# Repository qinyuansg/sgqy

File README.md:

# 🏠 HomeHero — Daily Tasks for House Helpers

> **Also in this repo:** [`fastpass/`](fastpass/) — the AGIL® Secure FastPass product site (kerb-to-gate journey explorer, traveller app demo, command console). See [`fastpass/README.md`](fastpass/README.md).

A simple, warm, mobile-first web app that helps a house helper know **what to do today**, tick tasks as done, and explain (in one tap) when something cannot be done — while giving the household full transparency on progress.

**Zero install, zero backend, zero cost.** Open `index.html` in any phone browser (or host it on GitHub Pages) and it just works. All data is saved on the device.

---

## Product vision (CPO perspective)

### The problem
Households coordinate daily chores with helpers through memory, paper lists, or long chat messages. Helpers — often with limited literacy and low tech confidence — struggle with text-heavy apps, and employers lack visibility into what got done and *why* something didn't.

### The users
| Persona | Need |
|---|---|
| **The Helper** (primary) | "Show me clearly what to do *now*, let me finish tasks with one tap, and make it feel good." |
| **The Employer** (secondary) | "Set up the routine once, then see progress and reasons transparently — without nagging." |

### Design principles
1. **Zero reading required to succeed.** Every task has a big emoji; every action is one large tap; reasons for "cannot do" are picture buttons, and typing is always optional.
2. **Time is the navigation.** The day flows visually Morning → Noon → Afternoon → Night with a colored timeline, a pulsing **NOW** badge, and auto-scroll to the current period. The helper never asks "what's next?"
3. **Every action gets a reward.** Apple-style spring animations, a drawn checkmark, a flying ⭐ +1, confetti bursts, haptic vibration, and a full celebration when the day is complete. Positive loops, never guilt.
4. **Honesty is a feature, not a failure.** "Cannot 😕" is a first-class button. Reporting a blocker (no supplies, machine broken…) earns a friendly "thank you for telling" — because a true status is more valuable than a fake tick.
5. **Transparency without surveillance.** The 7-day history shows completion bars and remarks for both parties. No GPS, no photos, no timers — trust-building, not policing.

---

## MVP features

- **⏰ Time-flow timeline** — tasks grouped Morning 🌅 / Noon ☀️ / Afternoon 🌤️ / Night 🌙 with a gradient timeline, current-period highlight, and auto-scroll.
- **✓ One-tap completion** — giant 58px tick button, springy checkmark draw, confetti, star reward, done timestamp. Tap again to undo mistakes.
- **😕 "Cannot do" flow** — bottom sheet with four picture reasons (🧴 no supplies, ⏰ no time, 🤒 not well, 🔧 broken) + optional free-text remark.
- **🎮 Gamification** — daily progress ring (Apple-Fitness style), ⭐ stars per task, 🔥 day streak for days where every task is actioned (done *or* honestly reported), escalating encouragement messages, full-screen celebration with confetti rain.
- **🔔 Reminders** — one tap on the bell enables browser notifications at the start of each period listing what's pending (fires while the app is open; see roadmap for push).
- **📅 Transparency** — 7-day history with completion bars, trophies for perfect days, and every "cannot do" reason surfaced with its remark.
- **⚙️ Employer setup** — manage the task list in-app: emoji picker, task name, time period. Changes apply instantly, persisted on-device.
- **📱 Installable** — web-app manifest lets it live on the home screen like a native app.

## Deliberate MVP cuts (roadmap)

| Next | Why later |
|---|---|
| Multi-language (Bahasa, Tagalog, Burmese, Sinhala…) | Highest-impact v1.1; the emoji-first UI keeps v1 usable meanwhile |
| Cloud sync + employer's own phone view | Needs accounts/backend; MVP proves the loop on one shared device |
| True push reminders (service worker / server push) | Browser limitations; in-app notifications validate the habit first |
| Photo proof (optional per task) | Useful but risks a surveillance feel — needs careful design |
| Weekly/rotating schedules (e.g. "change bedsheets — Mondays") | Data model supports it; UI simplicity first |
| Rewards marketplace (stars → real treats agreed with employer) | Requires employer buy-in mechanics |

## Success metrics
- **Activation:** helper completes ≥1 task on day one.
- **Habit:** ≥5 of 7 days with ≥80% tasks actioned (done *or* honestly skipped).
- **Trust:** share of skipped tasks carrying a reason (target: 100% — it's mandatory by design).
- **Delight proxy:** streak length distribution.

---

## Run & share it

**Easiest — share one file (works 100% offline):**
Send **`HomeHero.html`** to anyone over WhatsApp, email, or USB. They open it in any browser — no internet, no install, no other files needed. Progress saves on their own device. Rebuild it after changing the app:

```bash
python3 tools/build_single_file.py
```

**Hosted — GitHub Pages (offline after first visit):**
Enable Pages on this repo (Settings → Pages → deploy from branch), open the URL on the helper's phone, and "Add to Home Screen". A service worker (`sw.js`) caches the app, so it launches and works fully offline from then on.

**Local dev:**
```bash
python3 -m http.server 8000   # then visit http://localhost:8000
```

> Note: each device keeps its own data (tasks, progress, remarks) in `localStorage` — sharing the file shares the app, not the data. Cross-device sync is on the roadmap.

## Tech notes

- Vanilla HTML/CSS/JS — no build step, no dependencies, works offline after first load.
- Apple-inspired design system: iOS system palette, SF font stack, frosted-glass top bar, spring easing (`cubic-bezier(0.34, 1.56, 0.64, 1)`), 44pt+ touch targets, `prefers-reduced-motion` respected.
- State in `localStorage`: task list, per-day completion log (status/reason/remark/time), streak, reminder preference.

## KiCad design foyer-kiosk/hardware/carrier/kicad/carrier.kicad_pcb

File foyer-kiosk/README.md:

# Foyer VK-1 — visitor enrolment kiosk

A compact, premium self-service check-in kiosk for corporate office lobbies.
A visitor scans their invitation QR code (or registers as a walk-up), scans a
passport or ID card (OCR + NFC chip), has a face photo taken with liveness
detection, accepts the site rules, and gets a printed badge or mobile pass
while their host is notified through the visitor management system (VMS).

| | |
|---|---|
| Core unit | 250 W × 640 H × 200 D mm, ≈ 11 kg, anodised aluminium + 4 mm edge-to-edge glass |
| Compute | Raspberry Pi Compute Module 5 (4 GB / 32 GB eMMC, Wi-Fi 5 + BT 5.0), supply until ≥ Jan 2036 |
| Display | 13.3" 1920 × 1080 PCAP, portrait (Elo 1302L) |
| Identity | Full-page passport / ID reader, OCR + ePassport RFID (DESKO PENTA 4X Cube) |
| Face | RGB + NoIR 12 MP cameras with 850 nm IR flood for liveness |
| Invitation | Zebra DS55 2D scanner (reads QR from phone screens) |
| Badges | 80 mm thermal kiosk printer with cutter on a slide-out drawer |
| Audio | I2S class-D amplifier + speaker, 2 × I2S MEMS microphones (call reception) |
| Approach / status | ToF presence sensor, 24-LED status light bar |
| Connectivity | Gigabit Ethernet, Wi-Fi 2.4/5 GHz, Bluetooth; options: LTE fallback, HID NFC encoder |
| Power | Single PoE++ cable (802.3bt Type 4) or USB-C PD ≥ 65 W |
| Mounting | One core unit on desk, wall or floor kit (shared hang-on mount plate) |
| Security / privacy | Secure boot + full-disk encryption (CM5 OTP key), ATECC608B device identity, no PII at rest after sync |

## Repository map

```
foyer-kiosk/
├── hardware/
│   ├── interface-contract.md     HW⇄SW contract: buses, GPIOs, power policy (rev B)
│   ├── eda/                      circuit-as-code toolkit (ERC, schematic gen, PCB build, routing, DRC, fab)
│   ├── power/design_calcs.py     power-stage calculations (→ docs/power-design.md)
│   ├── carrier/                  FYR-CB-01 carrier board: carrier.py (circuit), build.py (layout+fab),
│   │                             kicad/ (KiCad 7 project), fab/ (gerbers, drill, BOM, CPL, STEP, PDFs)
│   ├── sensorbar/                FYR-SB-01 sensor bar: same structure
│   └── lib/                      vendored symbols + Foyer footprints (incl. CM5 socket)
├── mechanical/
│   ├── enclosure.py              parametric CadQuery model (enclosure + kits)
│   ├── build.py                  exports below
│   └── out/  step/ print/ dxf/ drawings/ renders/
├── software/                     enrolment app, device agent, OS image build (see software/README.md)
└── docs/                         spec, BOM, installation guide, maintenance manual, manufacturing,
                                  verification register, power design
```

## Requirement trace

| Requirement | How it is met | Where |
|---|---|---|
| Compact, modern, premium | 250 mm wide, edge-to-edge glass, anodised aluminium, no visible fasteners (lock hidden under the door lip, security screw under the mount) | `mechanical/`, renders |
| Locked-down kiosk OS, boots into the app | Raspberry Pi OS (arm64) image with cage + Chromium kiosk, hardened services | `software/os-image/` |
| QR or walk-up → ID + face → VMS → host notified → badge / mobile pass | Enrolment app + device agent with VMS adapter | `software/app`, `software/agent` |
| Publicly available, long-term compute | Raspberry Pi CM5, production to ≥ 2036 | `docs/bom-system.csv` |
| 10–13" portrait touch | 13.3" PCAP portrait | Elo 1302L |
| Camera with liveness | RGB + NoIR IMX708 pair + 850 nm IR flood on the sensor bar | `hardware/sensorbar` |
| QR reader, ID/passport reader (OCR + NFC), badge printer | DS55, DESKO PENTA 4X, Custom VKP80III; carrier USB 2 ×6 + USB 3 ×1 internal ports | carrier `J9–J12` |
| Speaker + mic | MAX98357A I2S amp + speaker header; 2 × ICS-43434 | carrier `U13`, sensor bar `MK1/2` |
| Proximity + status light | VL53L1X ToF wake; 24 × SK6812 light bar | sensor bar |
| GbE, 2.4/5 GHz Wi-Fi, BT | CM5 PHY + MagJack; CM5 wireless | carrier `J1` |
| LTE + NFC encoder (nice to have) | Internal USB ports + mounting positions | carrier `J11B`, `J12A` |
| Single PoE++ cable, USB-C PD alternative | Ag59812 PoE++ PD (12 V 89 W) + STUSB4500 PD sink → 12 V, ideal-diode OR | carrier power sheet |
| eMMC, encrypted | CM5 eMMC + secure-boot FDE (OTP key) | `docs/manufacturing.md` §4 |
| Wheelchair usable | Deck at 861 mm (ADA ≤ 864), reach mode keeps touch targets ≤ 1117 mm (≤ 1220), 2-hand-free document deck, audio prompts | GA drawing, app |
| No PII on device after sync | In-memory sessions, encrypted ≤ 24 h offline queue, wipe on sync | `software/agent` |
| Install < 30 min, one person, desk/wall/floor | Common hang-on mount plate, drilling template, zero-touch provisioning | `docs/installation-guide.md` |
| Front service, no tools, single lock | Lift-up head door captures the drop-down lectern door; one cam lock; thumbscrew/latch FRUs | `docs/maintenance-manual.md` |
| Paper < 1 min, modules < 5 min | Slide-out printer drawer; plug-in FRUs | maintenance manual §3–4 |
| Remote monitoring + OTA | Heartbeat + `/metrics`; signed OTA with rollback; unattended security updates | `software/` |
| Carrier board + mechanical outline | KiCad project, gerbers, outline DXF, board STEP | `hardware/carrier/` |
| Production enclosure (STEP + drawings) | STEP assembly + parts, GA drawing, DXFs | `mechanical/out/` |
| 3D-printed prototype (STL/3MF) + mounting kits | Split-to-bed STL + 3MF incl. desk/floor kits and mount plate | `mechanical/out/print/` |
| OS image that pulls latest updates | Build script fetches the latest Raspberry Pi OS Lite arm64, injects config; first boot installs + enables updates | `software/os-image/` |
| Fully sourceable, BOM | System BOM + PCBA BOMs with US distributors | `docs/bom-system.csv`, `hardware/*/fab/*-bom.csv` |
| Installation guide + maintenance manual | — | `docs/` |

## Status — read this before ordering anything

This is a complete **EVT design package**, generated and checked in software.
No unit has been built or powered. See [`docs/verification-register.md`](docs/verification-register.md):
three footprints (PoE MagJack, PoE++ module, IR emitter) and two application
circuits must be checked against vendor drawings that were not retrievable in
the design environment, and the autorouted PCBs need a layout engineer's pass
for controlled-impedance pairs and power copper before fabrication.

| Board | KiCad DRC | Open items |
|---|---|---|
| Sensor bar FYR-SB-01 | 0 errors, 0 unconnected | layout review (D-1) |
| Carrier FYR-CB-01 | 0 clearance/hole errors, **42 unconnected** | hand-route the 42 listed connections + layout review (D-1, ≈ 3 days) |

## Rebuilding everything

```bash
# electronics (needs KiCad 7 + Java; Freerouting jar at /opt/tools/freerouting.jar)
/usr/bin/python3 hardware/carrier/build.py all
/usr/bin/python3 hardware/sensorbar/build.py all
python3 hardware/power/design_calcs.py
# mechanics (needs cadquery, numpy, pillow; rsvg-convert)
python3 mechanical/build.py
# software / OS image: see software/README.md
```

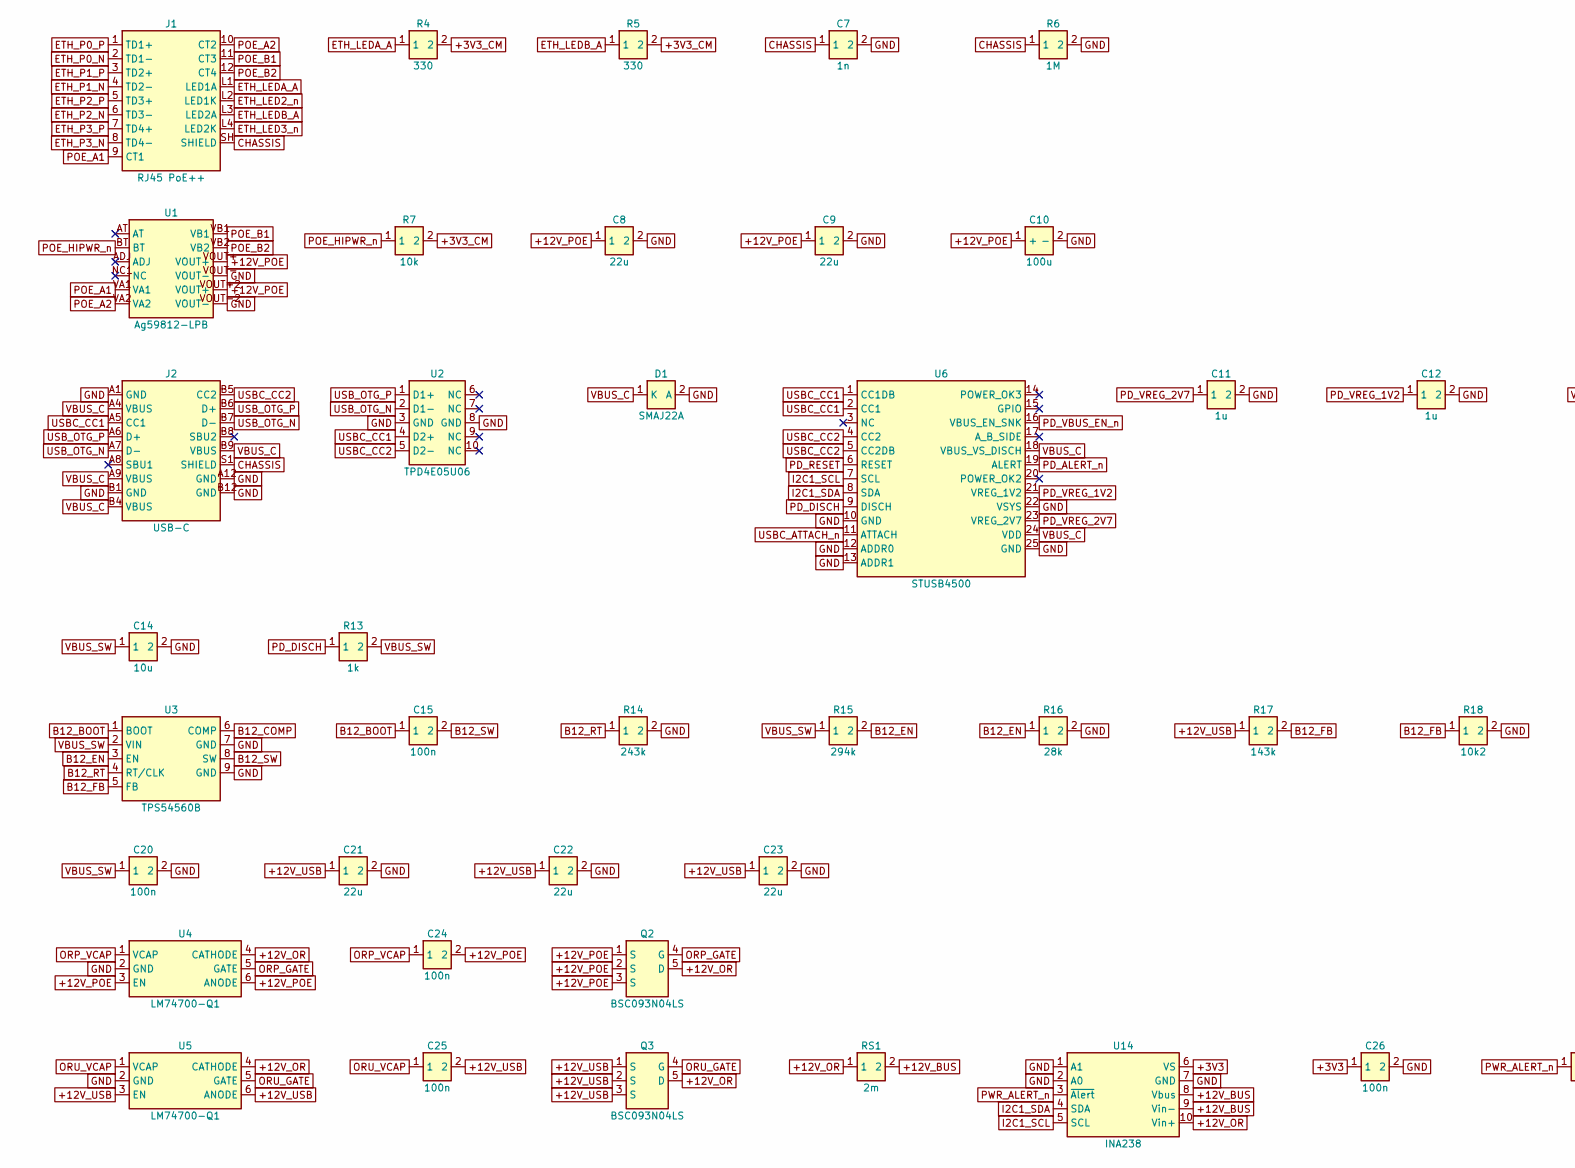
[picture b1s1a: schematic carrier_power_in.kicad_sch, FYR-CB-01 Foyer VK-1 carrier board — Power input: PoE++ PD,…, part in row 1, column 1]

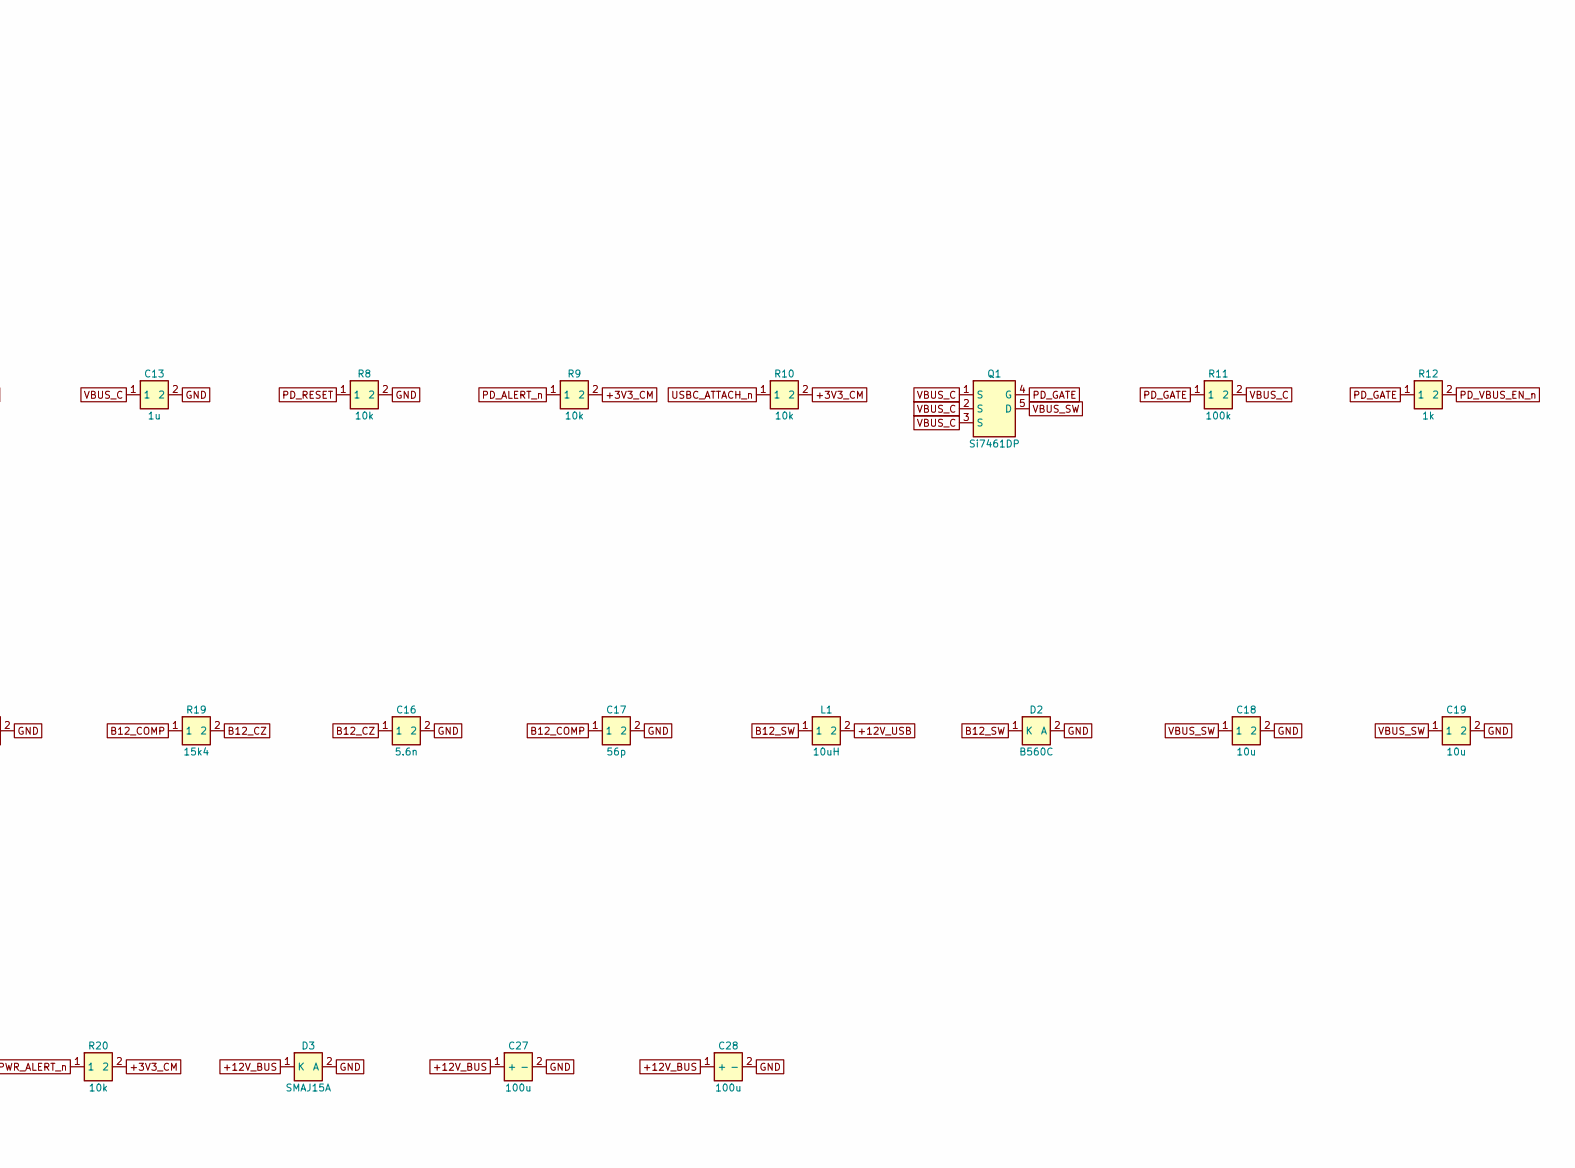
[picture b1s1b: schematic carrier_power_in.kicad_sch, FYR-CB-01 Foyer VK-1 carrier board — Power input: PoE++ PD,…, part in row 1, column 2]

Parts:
C7: 1n; C_1206_3216Metric
C8, C9, C21, C22, C23: 22u; C_1210_3225Metric
C10, C27, C28: 100u; CP_Elec_6.3x7.7; MPN EEH-ZA1E101XP
C11, C12: 1u; C_0402_1005Metric
C13: 1u; C_0603_1608Metric
C14, C18, C19: 10u; C_1210_3225Metric
C15, C20: 100n; C_0603_1608Metric
C16: 5.6n; C_0402_1005Metric
C17: 56p; C_0402_1005Metric
C24, C25, C26: 100n; C_0402_1005Metric
D1: SMAJ22A; D_SMA; MPN SMAJ22A
D2: B560C; D_SMC; MPN B560C-13-F
D3: SMAJ15A; D_SMA; MPN SMAJ15A
J1: RJ45 PoE++; Bel_0826-1X1T-HS-F_PROVISIONAL; MPN 0826-1X1T-HS-F
J2: USB-C; USB_C_Receptacle_GCT_USB4085; MPN USB4085-GF-A
L1: 10uH; L_Coilcraft_XAL1010-XXX; MPN XAL1010-103MEB
Q1: Si7461DP; PowerPAK_SO-8_Single; MPN SI7461DP-T1-GE3
Q2, Q3: BSC093N04LS; TDSON-8-1; MPN BSC093N04LSGATMA1
R4, R5: 330; R_0402_1005Metric
R6: 1M; R_1206_3216Metric
R7, R8, R9, R10, R20: 10k; R_0402_1005Metric
R11: 100k; R_0402_1005Metric
R12: 1k; R_0402_1005Metric
R13: 1k; R_0603_1608Metric
R14: 243k; R_0402_1005Metric
R15: 294k; R_0402_1005Metric
R16: 28k; R_0402_1005Metric
R17: 143k; R_0402_1005Metric
R18: 10k2; R_0402_1005Metric
R19: 15k4; R_0402_1005Metric
RS1: 2m; R_2512_6332Metric; MPN WSL2512R0020FEA
U1: Ag59812-LPB; Silvertel_Ag59812-LPB_PROVISIONAL; MPN Ag59812-LPB
U2: TPD4E05U06; USON-10_2.5x1.0mm_P0.5mm; MPN TPD4E05U06DQAR
U3: TPS54560B; Texas_R-PDSO-G8_EP2.95x4.9mm_Mask2.4x3.1mm_ThermalVias; MPN TPS54560BDDAR
U4, U5: LM74700-Q1; SOT-23-6; MPN LM74700QDBVRQ1
U6: STUSB4500; QFN-24-1EP_4x4mm_P0.5mm_EP2.7x2.7mm; MPN STUSB4500QTR
U14: INA238; TSSOP-10_3x3mm_P0.5mm; MPN INA238AIDGSR

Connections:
+3V3: C26.1, U14.6 (VS); also elsewhere on the board
+3V3_CM: R4.2, R5.2, R7.2, R9.2, R10.2, R20.2; also elsewhere on the board
+12V_BUS: C27.1 (+), C28.1 (+), D3.1 (K), RS1.2, U14.8 (Vbus), U14.9 (Vin-); also elsewhere on the board
+12V_OR: Q2.5 (D), Q3.5 (D), RS1.1, U4.4 (CATHODE), U5.4 (CATHODE), U14.10 (Vin+)
+12V_POE: C8.1, C9.1, C10.1 (+), C24.2, Q2.1 (S), Q2.2 (S), Q2.3 (S), U1.VOUT+, U1.VOUT+2 (VOUT+), U4.3 (EN), U4.6 (ANODE)
+12V_USB: C21.1, C22.1, C23.1, C25.2, L1.2, Q3.1 (S), Q3.2 (S), Q3.3 (S), R17.1, U5.3 (EN), U5.6 (ANODE)
B12_BOOT: C15.1, U3.1 (BOOT)
B12_COMP: C17.1, R19.1, U3.6 (COMP)
B12_CZ: C16.1, R19.2
B12_EN: R15.2, R16.1, U3.3 (EN)
B12_FB: R17.2, R18.1, U3.5 (FB)
B12_RT: R14.1, U3.4 (RT/CLK)
B12_SW: C15.2, D2.1 (K), L1.1, U3.8 (SW)
CHASSIS: C7.1, J1.SH (SHIELD), J2.S1 (SHIELD), R6.1; also elsewhere on the board
ETH_LED2_n: J1.L2 (LED1K); also elsewhere on the board
ETH_LED3_n: J1.L4 (LED2K); also elsewhere on the board
ETH_LEDA_A: J1.L1 (LED1A), R4.1
ETH_LEDB_A: J1.L3 (LED2A), R5.1
ETH_P0_N: J1.2 (TD1-); also elsewhere on the board
ETH_P0_P: J1.1 (TD1+); also elsewhere on the board
ETH_P1_N: J1.4 (TD2-); also elsewhere on the board
ETH_P1_P: J1.3 (TD2+); also elsewhere on the board
ETH_P2_N: J1.6 (TD3-); also elsewhere on the board
ETH_P2_P: J1.5 (TD3+); also elsewhere on the board
ETH_P3_N: J1.8 (TD4-); also elsewhere on the board
ETH_P3_P: J1.7 (TD4+); also elsewhere on the board
GND: C7.2, C8.2, C9.2, C10.2 (-), C11.2, C12.2, C13.2, C14.2, C16.2, C17.2, C18.2, C19.2, C20.2, C21.2, C22.2, C23.2, C26.2, C27.2 (-), C28.2 (-), D1.2 (A), D2.2 (A), D3.2 (A), J2.A1 (GND), J2.A12 (GND), J2.B1 (GND), J2.B12 (GND), R6.2, R8.2, R14.2, R16.2, R18.2, U1.VOUT-, U1.VOUT-2 (VOUT-), U2.3 (GND), U2.8 (GND), U3.7 (GND), U3.9 (GND), U4.2 (GND), U5.2 (GND), U6.10 (GND), U6.12 (ADDR0), U6.13 (ADDR1), U6.22 (VSYS), U6.25 (GND), U14.1 (A1), U14.2 (A0), U14.7 (GND); also elsewhere on the board
I2C1_SCL: U6.7 (SCL), U14.5 (SCL); also elsewhere on the board
I2C1_SDA: U6.8 (SDA), U14.4 (SDA); also elsewhere on the board
ORP_GATE: Q2.4 (G), U4.5 (GATE)
ORP_VCAP: C24.1, U4.1 (VCAP)
ORU_GATE: Q3.4 (G), U5.5 (GATE)
ORU_VCAP: C25.1, U5.1 (VCAP)
PD_ALERT_n: R9.1, U6.19 (ALERT); also elsewhere on the board
PD_DISCH: R13.1, U6.9 (DISCH)
PD_GATE: Q1.4 (G), R11.1, R12.1
PD_RESET: R8.1, U6.6 (RESET)
PD_VBUS_EN_n: R12.2, U6.16 (VBUS_EN_SNK)
PD_VREG_1V2: C12.1, U6.21 (VREG_1V2)
PD_VREG_2V7: C11.1, U6.23 (VREG_2V7)
POE_A1: J1.9 (CT1), U1.VA1
POE_A2: J1.10 (CT2), U1.VA2
POE_B1: J1.11 (CT3), U1.VB1
POE_B2: J1.12 (CT4), U1.VB2
POE_HIPWR_n: R7.1, U1.BT; also elsewhere on the board
PWR_ALERT_n: R20.1, U14.3 (~Alert); also elsewhere on the board
USBC_ATTACH_n: R10.1, U6.11 (ATTACH); also elsewhere on the board
USBC_CC1: J2.A5 (CC1), U2.4 (D2+), U6.1 (CC1DB), U6.2 (CC1)
USBC_CC2: J2.B5 (CC2), U2.5 (D2-), U6.4 (CC2), U6.5 (CC2DB)
USB_OTG_N: J2.A7 (D-), J2.B7 (D-), U2.2 (D1-); also elsewhere on the board
USB_OTG_P: J2.A6 (D+), J2.B6 (D+), U2.1 (D1+); also elsewhere on the board
VBUS_C: C13.1, D1.1 (K), J2.A4 (VBUS), J2.A9 (VBUS), J2.B4 (VBUS), J2.B9 (VBUS), Q1.1 (S), Q1.2 (S), Q1.3 (S), R11.2, U6.18 (VBUS_VS_DISCH), U6.24 (VDD)
VBUS_SW: C14.1, C18.1, C19.1, C20.1, Q1.5 (D), R13.2, R15.1, U3.2 (VIN)

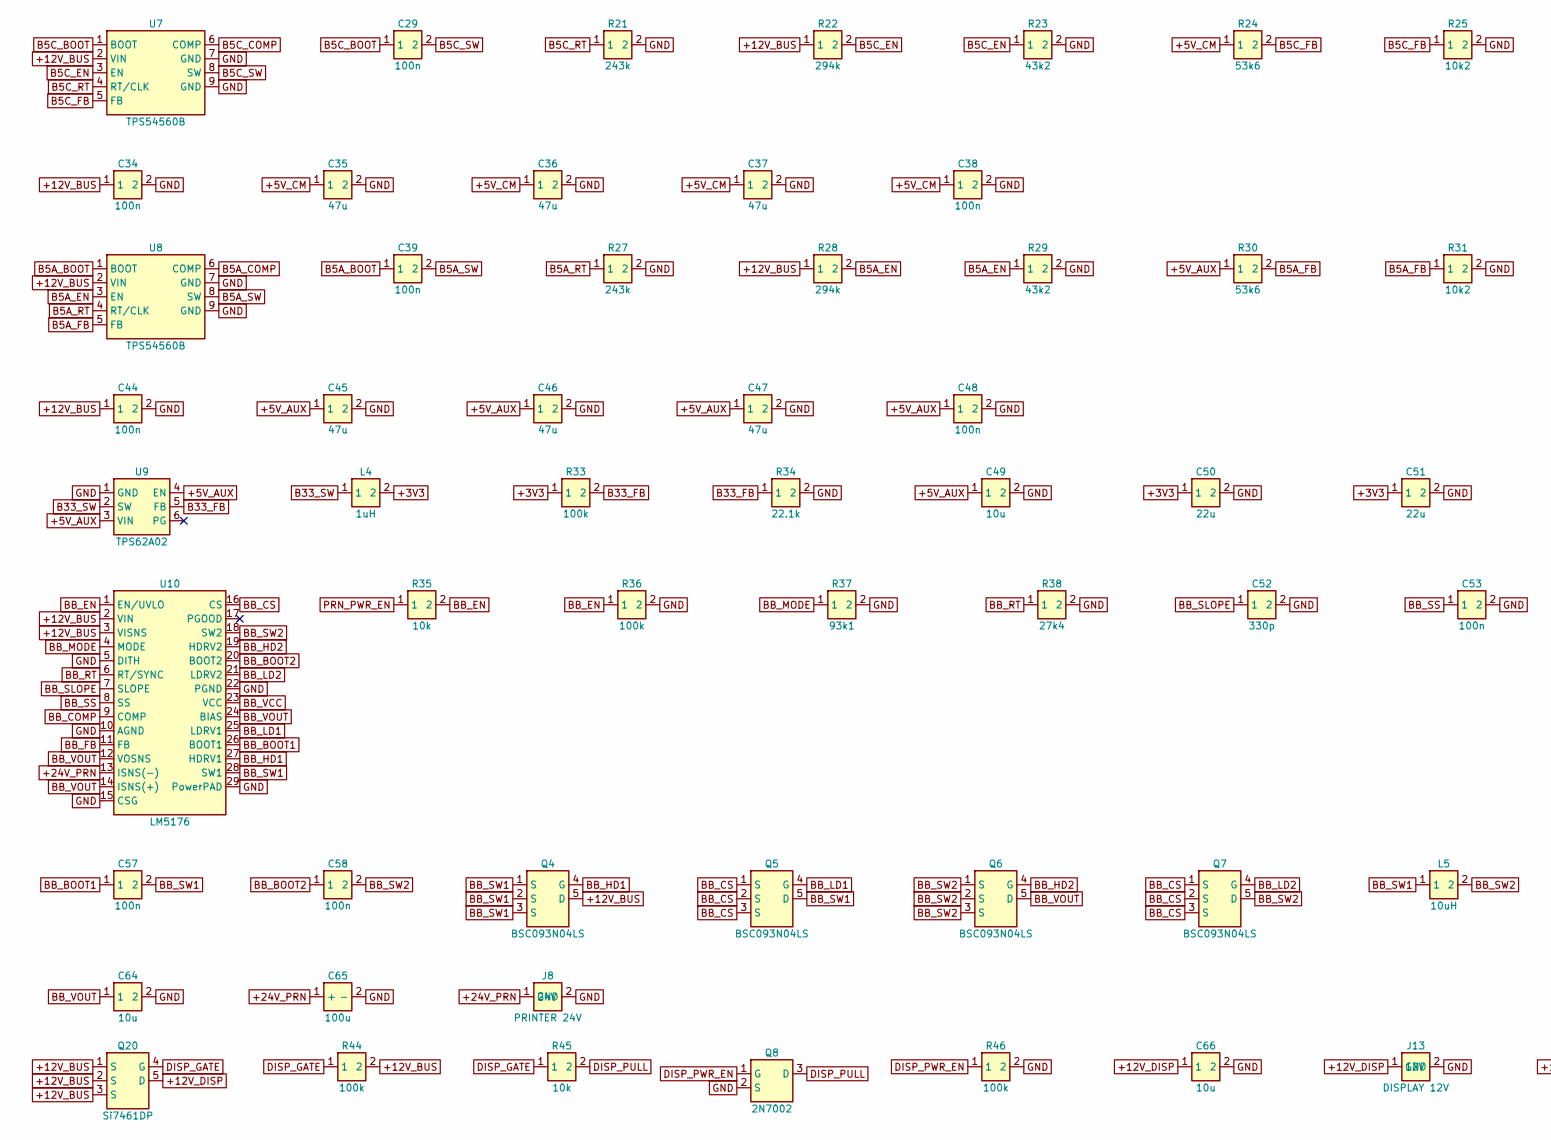
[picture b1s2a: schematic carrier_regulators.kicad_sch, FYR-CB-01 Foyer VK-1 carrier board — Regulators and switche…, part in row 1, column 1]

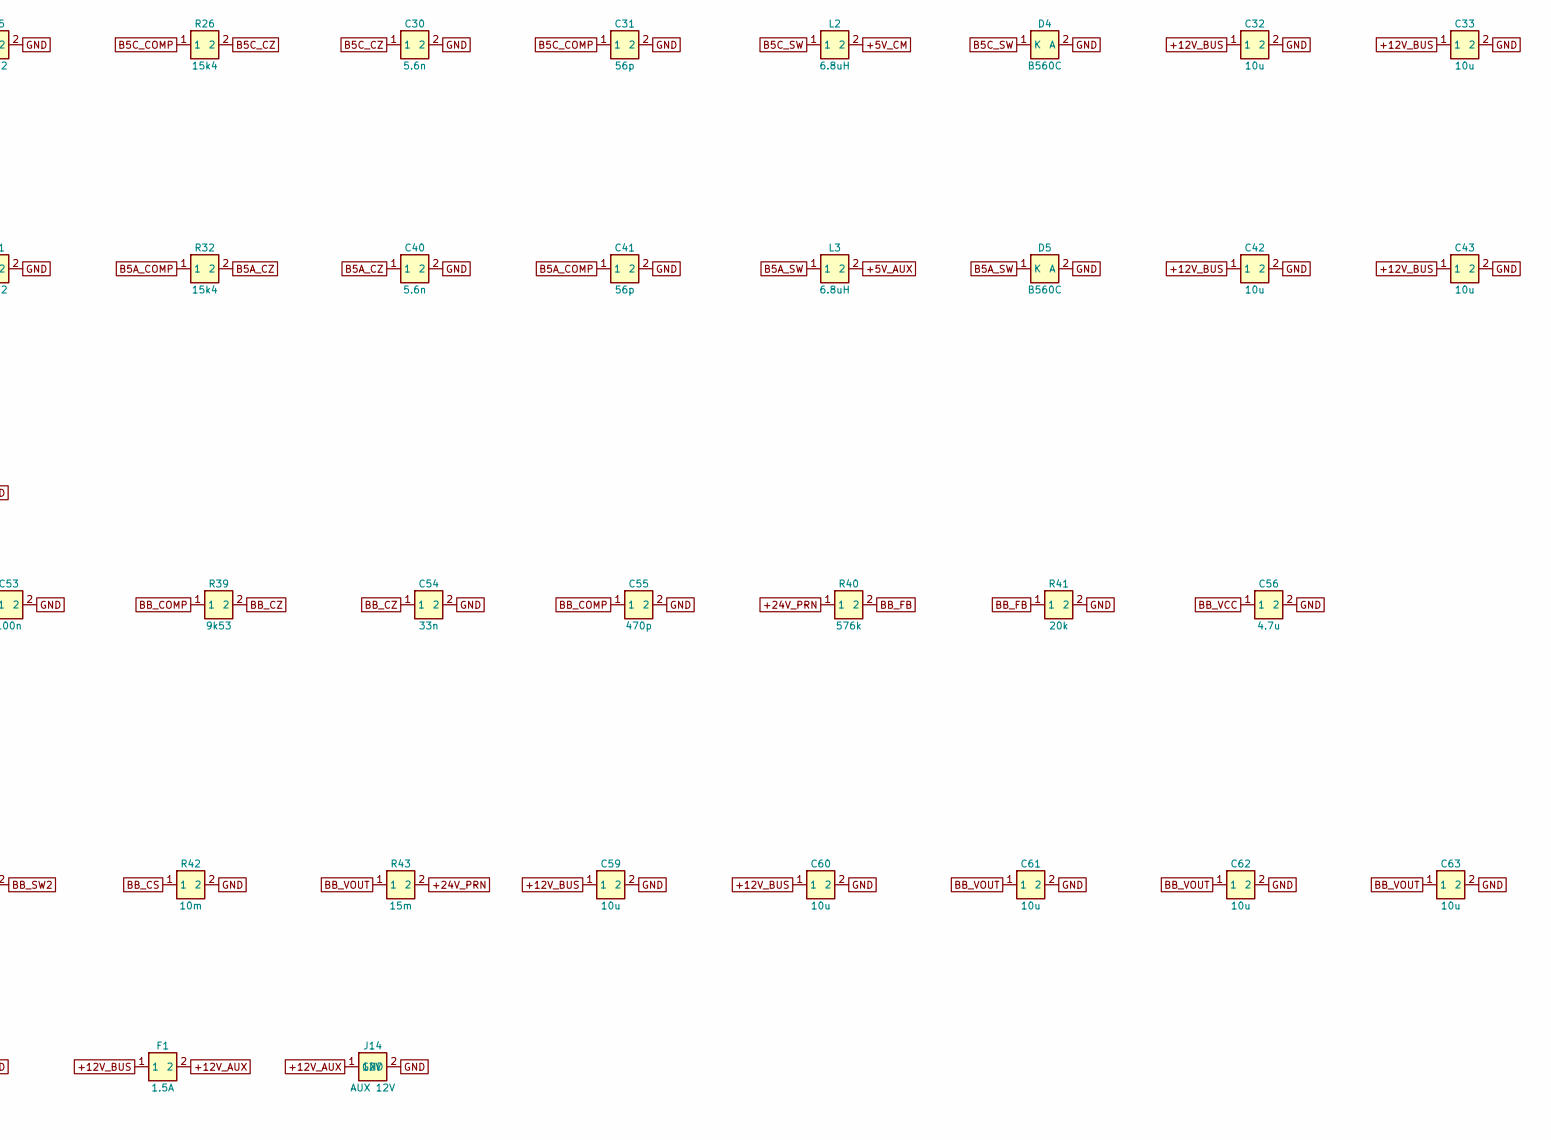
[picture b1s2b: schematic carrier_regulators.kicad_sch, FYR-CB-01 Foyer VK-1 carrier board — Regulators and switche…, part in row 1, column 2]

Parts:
C29, C34, C39, C44, C57, C58: 100n; C_0603_1608Metric
C30, C40: 5.6n; C_0402_1005Metric
C31, C41: 56p; C_0402_1005Metric
C32, C33, C42, C43, C59, C60, C61, C62, C63, C64, C66: 10u; C_1210_3225Metric
C35, C36, C37, C45, C46, C47: 47u; C_1210_3225Metric
C38, C48, C53: 100n; C_0402_1005Metric
C49: 10u; C_0805_2012Metric
C50, C51: 22u; C_0805_2012Metric
C52: 330p; C_0402_1005Metric
C54: 33n; C_0402_1005Metric
C55: 470p; C_0402_1005Metric
C56: 4.7u; C_0603_1608Metric
C65: 100u; CP_Elec_8x10; MPN EEH-ZA1V101P
D4, D5: B560C; D_SMC; MPN B560C-13-F
F1: 1.5A; Fuse_1812_4532Metric; MPN MF-MSMF150/24X-2
J8: PRINTER 24V; Molex_Micro-Fit_3.0_43650-0200_1x02_P3.00mm_Horizontal; MPN 43650-0200
J13: DISPLAY 12V; Molex_Micro-Fit_3.0_43650-0200_1x02_P3.00mm_Horizontal; MPN 43650-0200
J14: AUX 12V; Molex_Micro-Fit_3.0_43650-0200_1x02_P3.00mm_Horizontal; MPN 43650-0200
L2, L3: 6.8uH; L_Coilcraft_XAL1010-XXX; MPN XAL1010-682MEB
L4: 1uH; L_Coilcraft_XAL4020-XXX; MPN XAL4020-102MEB
L5: 10uH; L_Coilcraft_XAL1010-XXX; MPN XAL1010-103MEB
Q4, Q5, Q6, Q7: BSC093N04LS; TDSON-8-1; MPN BSC093N04LSGATMA1
Q8: 2N7002; SOT-23; MPN 2N7002LT1G
Q20: Si7461DP; PowerPAK_SO-8_Single; MPN SI7461DP-T1-GE3
R21, R27: 243k; R_0402_1005Metric
R22, R28: 294k; R_0402_1005Metric
R23, R29: 43k2; R_0402_1005Metric
R24, R30: 53k6; R_0402_1005Metric
R25, R31: 10k2; R_0402_1005Metric
R26, R32: 15k4; R_0402_1005Metric
R33, R36, R44, R46: 100k; R_0402_1005Metric
R34: 22.1k; R_0402_1005Metric
R35, R45: 10k; R_0402_1005Metric
R37: 93k1; R_0402_1005Metric
R38: 27k4; R_0402_1005Metric
R39: 9k53; R_0402_1005Metric
R40: 576k; R_0402_1005Metric
R41: 20k; R_0402_1005Metric
R42: 10m; R_2512_6332Metric; MPN WSLP2512R0100FE
R43: 15m; R_2512_6332Metric; MPN WSLP2512R0150FE
U7, U8: TPS54560B; Texas_R-PDSO-G8_EP2.95x4.9mm_Mask2.4x3.1mm_ThermalVias; MPN TPS54560BDDAR
U9: TPS62A02; SOT-563; MPN TPS62A02DRLR
U10: LM5176; HTSSOP-28-1EP_4.4x9.7mm_P0.65mm_EP3.4x9.5mm_ThermalVias; MPN LM5176PWPR

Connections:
+3V3: C50.1, C51.1, L4.2, R33.1; also elsewhere on the board
+5V_AUX: C45.1, C46.1, C47.1, C48.1, C49.1, L3.2, R30.1, U9.3 (VIN), U9.4 (EN); also elsewhere on the board
+5V_CM: C35.1, C36.1, C37.1, C38.1, L2.2, R24.1; also elsewhere on the board
+12V_AUX: F1.2, J14.1 (12V)
+12V_BUS: C32.1, C33.1, C34.1, C42.1, C43.1, C44.1, C59.1, C60.1, F1.1, Q4.5 (D), Q20.1 (S), Q20.2 (S), Q20.3 (S), R22.1, R28.1, R44.2, U7.2 (VIN), U8.2 (VIN), U10.2 (VIN), U10.3 (VISNS); also elsewhere on the board
+12V_DISP: C66.1, J13.1 (12V), Q20.5 (D)
+24V_PRN: C65.1 (+), J8.1 (24V), R40.1, R43.2, U10.13 (ISNS(-))
B5A_BOOT: C39.1, U8.1 (BOOT)
B5A_COMP: C41.1, R32.1, U8.6 (COMP)
B5A_CZ: C40.1, R32.2
B5A_EN: R28.2, R29.1, U8.3 (EN)
B5A_FB: R30.2, R31.1, U8.5 (FB)
B5A_RT: R27.1, U8.4 (RT/CLK)
B5A_SW: C39.2, D5.1 (K), L3.1, U8.8 (SW)
B5C_BOOT: C29.1, U7.1 (BOOT)
B5C_COMP: C31.1, R26.1, U7.6 (COMP)
B5C_CZ: C30.1, R26.2
B5C_EN: R22.2, R23.1, U7.3 (EN)
B5C_FB: R24.2, R25.1, U7.5 (FB)
B5C_RT: R21.1, U7.4 (RT/CLK)
B5C_SW: C29.2, D4.1 (K), L2.1, U7.8 (SW)
B33_FB: R33.2, R34.1, U9.5 (FB)
B33_SW: L4.1, U9.2 (SW)
BB_BOOT1: C57.1, U10.26 (BOOT1)
BB_BOOT2: C58.1, U10.20 (BOOT2)
BB_COMP: C55.1, R39.1, U10.9 (COMP)
BB_CS: Q5.1 (S), Q5.2 (S), Q5.3 (S), Q7.1 (S), Q7.2 (S), Q7.3 (S), R42.1, U10.16 (CS)
BB_CZ: C54.1, R39.2
BB_EN: R35.2, R36.1, U10.1 (EN/UVLO)
BB_FB: R40.2, R41.1, U10.11 (FB)
BB_HD1: Q4.4 (G), U10.27 (HDRV1)
BB_HD2: Q6.4 (G), U10.19 (HDRV2)
BB_LD1: Q5.4 (G), U10.25 (LDRV1)
BB_LD2: Q7.4 (G), U10.21 (LDRV2)
BB_MODE: R37.1, U10.4 (MODE)
BB_RT: R38.1, U10.6 (RT/SYNC)
BB_SLOPE: C52.1, U10.7 (SLOPE)
BB_SS: C53.1, U10.8 (SS)
BB_SW1: C57.2, L5.1, Q4.1 (S), Q4.2 (S), Q4.3 (S), Q5.5 (D), U10.28 (SW1)
BB_SW2: C58.2, L5.2, Q6.1 (S), Q6.2 (S), Q6.3 (S), Q7.5 (D), U10.18 (SW2)
BB_VCC: C56.1, U10.23 (VCC)
BB_VOUT: C61.1, C62.1, C63.1, C64.1, Q6.5 (D), R43.1, U10.12 (VOSNS), U10.14 (ISNS(+)), U10.24 (BIAS)
DISP_GATE: Q20.4 (G), R44.1, R45.1
DISP_PULL: Q8.3 (D), R45.2
DISP_PWR_EN: Q8.1 (G), R46.1; also elsewhere on the board
GND: C30.2, C31.2, C32.2, C33.2, C34.2, C35.2, C36.2, C37.2, C38.2, C40.2, C41.2, C42.2, C43.2, C44.2, C45.2, C46.2, C47.2, C48.2, C49.2, C50.2, C51.2, C52.2, C53.2, C54.2, C55.2, C56.2, C59.2, C60.2, C61.2, C62.2, C63.2, C64.2, C65.2 (-), C66.2, D4.2 (A), D5.2 (A), J8.2 (GND), J13.2 (GND), J14.2 (GND), Q8.2 (S), R21.2, R23.2, R25.2, R27.2, R29.2, R31.2, R34.2, R36.2, R37.2, R38.2, R41.2, R42.2, R46.2, U7.7 (GND), U7.9 (GND), U8.7 (GND), U8.9 (GND), U9.1 (GND), U10.5 (DITH), U10.10 (AGND), U10.15 (CSG), U10.22 (PGND), U10.29 (PowerPAD); also elsewhere on the board
PRN_PWR_EN: R35.1; also elsewhere on the board
